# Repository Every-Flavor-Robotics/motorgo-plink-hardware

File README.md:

# MotorGo Plink
## The aim of this project is to make a 4 DC motor drive compatible with the motorgo ecosystem - specifically designed for beginner roboticists.  It should be the form factor of a pihat, but capable of operating entirely on it's own as well. Currently testing release version 1.0!

### Feature list:
- Esp32s3 with Wifi and BT connectivity
- Form factor of a PiHat (we do not currently have the EEPROM requirements of the PiHat Spec)
- DC barrel jack and on-board buck from 6-17V into 5.1V up to 6A  (enough to power pi4 and pi5)
- 9 dof IMU  (LSM6DSOTR-C accel and gyro  +  LIS3MDLTR mag)
- USB-C programming compatible with arduino IDE
- Qwiic port x2 for easy integration with sensors
- Full gpio breakout on 40Pin header + full RPi GPIO passthrough if using as a hat
- 4 bidirectional DC motor channels up to 2A each channel
- 4 Encoder ports for use with EncoderGo 5pin jst for close loop feedback on each motor

### Schematics: 
- Top level

- Motor drivers

- IMU 

- Power system 

- connectors 

### Layout:
- Top - signals components and power

- Inner 1 - GND (I left faint top layer to show ground relative to traces)

- Inner 2 - GND and a tiny tiny power traces where needed

- Bottom - signals and power

- Dimensions

- Full

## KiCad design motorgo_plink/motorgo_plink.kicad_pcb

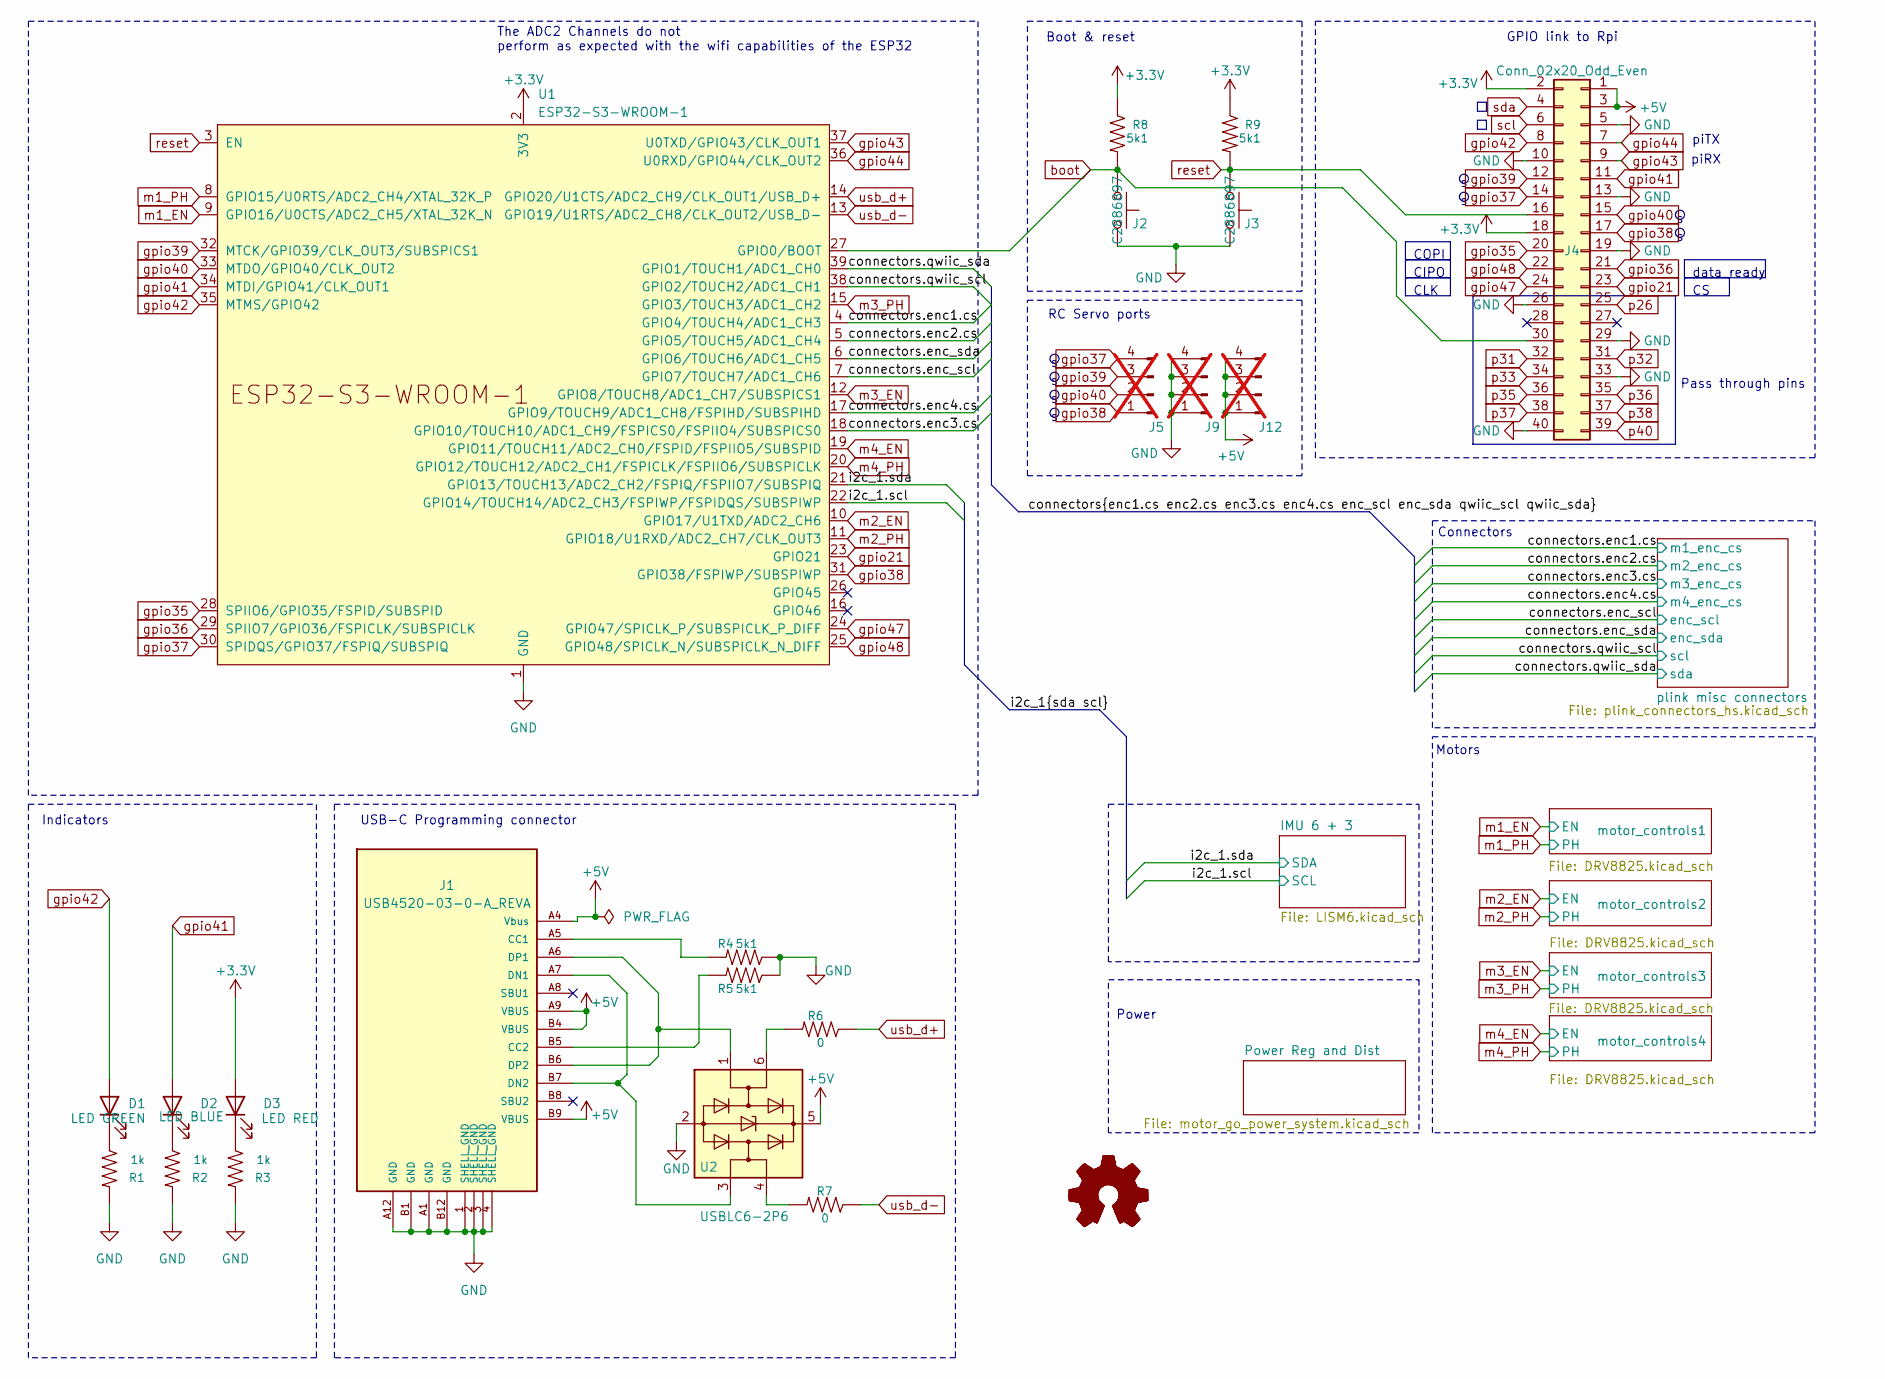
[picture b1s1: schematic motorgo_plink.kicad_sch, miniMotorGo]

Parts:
D1: LED GREEN; LED_0805_2012Metric; LCSC_Part_Number C84259
D2: LED BLUE; LED_0805_2012Metric; LCSC_Part_Number C84260
D3: LED RED; LED_0805_2012Metric; LCSC_Part_Number C84256
J1: USB4520-03-0-A_REVA; USB-C-SMD_TYPEC-303-ACP16; LCSC_Part_Number C720628
J2, J3: C2886897; SW_SPST_TL3342; LCSC_Part_Number C2886897
J4: Conn_02x20_Odd_Even; PinSocket_2x20_P2.54mm_Vertical_SMD; LCSC_Part_Number C3975165
J5, J9, J12: Conn_01x04_Pin; PinHeader_1x04_P2.54mm_Vertical; not fitted
R1, R2, R3: 1k; R_0402_1005Metric; LCSC_Part_Number C11702
R4, R5, R8, R9: 5k1; R_0402_1005Metric; LCSC_Part_Number C25905
R6, R7: 0; R_0402_1005Metric; LCSC_Part_Number C3017451
U1: ESP32-S3-WROOM-1; LCSC_Part_Number C2913198
U2: USBLC6-2P6; SOT-666; LCSC_Part_Number C2827693

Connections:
+3.3V: D3.2 (A), J4.2, J4.18, R8.1, R9.1, U1.2 (3V3); also elsewhere on the board
+5V: J1.A4 (Vbus), J1.A9 (VBUS), J1.B4 (VBUS), J1.B9 (VBUS), J4.1, J4.3, J12.1, J12.2, J12.3, J12.4, U2.5 (VBUS); also elsewhere on the board
/connectors.enc1.cs: U1.4 (GPIO4/TOUCH4/ADC1_CH3); also elsewhere on the board
/connectors.enc2.cs: U1.5 (GPIO5/TOUCH5/ADC1_CH4); also elsewhere on the board
/connectors.enc3.cs: U1.18 (GPIO10/TOUCH10/ADC1_CH9/FSPICS0/FSPIIO4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); also elsewhere on the board
/connectors.enc4.cs: U1.17 (GPIO9/TOUCH9/ADC1_CH8/FSPIHD/SUBSPIHD); also elsewhere on the board
/connectors.enc_scl: U1.7 (GPIO7/TOUCH7/ADC1_CH6); also elsewhere on the board
/connectors.enc_sda: U1.6 (GPIO6/TOUCH6/ADC1_CH5); also elsewhere on the board
/i2c_1.scl: U1.22 (GPIO14/TOUCH14/ADC2_CH3/FSPIWP/FSPIDQS/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); also elsewhere on the board
/i2c_1.sda: U1.21 (GPIO13/TOUCH13/ADC2_CH2/FSPIQ/FSPIIO7/S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); also elsewhere on the board
GND: J1.1 (SHELL_GND), J1.2 (SHELL_GND), J1.3 (SHELL_GND), J1.4 (SHELL_GND), J1.A1 (GND), J1.A12 (GND), J1.B1 (GND), J1.B12 (GND), J2.1, J3.2, J4.5, J4.10, J4.13, J4.19, J4.26, J4.29, J4.33, J4.40, J9.1, J9.2, J9.3, J9.4, R1.2, R2.2, R3.2, R4.1, R5.1, U1.1 (GND), U1.40 (GND), U1.41 (GND), U2.2 (GND); also elsewhere on the board
unnamed: D1.1 (K), R1.1
unnamed: D2.1 (K), R2.1
unnamed: D3.1 (K), R3.1
unnamed: J1.A5 (CC1), R4.2
unnamed: J1.B5 (CC2), R5.2
unnamed: J1.A7 (DN1), J1.B7 (DN2), U2.3 (I/O2)
unnamed: J1.A6 (DP1), J1.B6 (DP2), U2.1 (I/O1)
unnamed: R6.2, U2.6 (I/O1)
unnamed: R7.2, U2.4 (I/O2)
boot: J2.2, J4.30, R8.2, U1.27 (GPIO0/BOOT); also elsewhere on the board
gpio21: J4.23, U1.23 (GPIO21); also elsewhere on the board
gpio35: J4.20, U1.28 (SPIIO6/GPIO35/FSPID/SUBSPID); also elsewhere on the board
gpio36: J4.21, U1.29 (SPIIO7/GPIO36/FSPICLK/SUBSPICLK); also elsewhere on the board
gpio37: J4.14, J5.4, U1.30 (SPIDQS/GPIO37/FSPIQ/SUBSPIQ); also elsewhere on the board
gpio38: J4.17, J5.1, U1.31 (GPIO38/FSPIWP/SUBSPIWP); also elsewhere on the board
gpio39: J4.12, J5.3, U1.32 (MTCK/GPIO39/CLK_OUT3/SUBSPICS1); also elsewhere on the board
gpio40: J4.15, J5.2, U1.33 (MTDO/GPIO40/CLK_OUT2); also elsewhere on the board
gpio41: D2.2 (A), J4.11, U1.34 (MTDI/GPIO41/CLK_OUT1); also elsewhere on the board
gpio42: D1.2 (A), J4.8, U1.35 (MTMS/GPIO42); also elsewhere on the board
gpio43: J4.9, U1.37 (U0TXD/GPIO43/CLK_OUT1); also elsewhere on the board
gpio44: J4.7, U1.36 (U0RXD/GPIO44/CLK_OUT2); also elsewhere on the board
gpio47: J4.24, U1.24 (GPIO47/SPICLK_P/SUBSPICLK_P_DIFF); also elsewhere on the board
gpio48: J4.22, U1.25 (GPIO48/SPICLK_N/SUBSPICLK_N_DIFF); also elsewhere on the board
m1_EN: U1.9 (GPIO16/U0CTS/ADC2_CH5/XTAL_32K_N); also elsewhere on the board
m1_PH: U1.8 (GPIO15/U0RTS/ADC2_CH4/XTAL_32K_P); also elsewhere on the board
m2_EN: U1.10 (GPIO17/U1TXD/ADC2_CH6); also elsewhere on the board
m2_PH: U1.11 (GPIO18/U1RXD/ADC2_CH7/CLK_OUT3); also elsewhere on the board
m3_EN: U1.12 (GPIO8/TOUCH8/ADC1_CH7/SUBSPICS1); also elsewhere on the board
m3_PH: U1.15 (GPIO3/TOUCH3/ADC1_CH2); also elsewhere on the board
m4_EN: U1.19 (GPIO11/TOUCH11/ADC2_CH0/FSPID/FSPIIO5/S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); also elsewhere on the board
m4_PH: U1.20 (GPIO12/TOUCH12/ADC2_CH1/FSPICLK/FSPIIO6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); also elsewhere on the board
p26: J4.25; also elsewhere on the board
p31: J4.32; also elsewhere on the board
p32: J4.31; also elsewhere on the board
p33: J4.34; also elsewhere on the board
p35: J4.36; also elsewhere on the board
p36: J4.35; also elsewhere on the board
p37: J4.38; also elsewhere on the board
p38: J4.37; also elsewhere on the board
p40: J4.39; also elsewhere on the board
reset: J3.1, J4.16, R9.2, U1.3 (EN); also elsewhere on the board
scl: J4.6, U1.38 (GPIO2/TOUCH2/ADC1_CH1); also elsewhere on the board
sda: J4.4, U1.39 (GPIO1/TOUCH1/ADC1_CH0); also elsewhere on the board
usb_d+: R6.1, U1.14 (GPIO20/U1CTS/ADC2_CH9/CLK_OUT1/USB_D+)
usb_d-: R7.1, U1.13 (GPIO19/U1RTS/ADC2_CH8/CLK_OUT2/USB_D-)

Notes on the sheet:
data_ready
CLK
COPI
CIPO
USB-C Programming connector
Motors
Power
Boot & reset
Indicators
piRX
piTX
The ADC2 Channels do not perform as expected with the wifi capabilities of the ESP32
Pass through pins
Connectors
RC Servo ports
GPIO link to Rpi

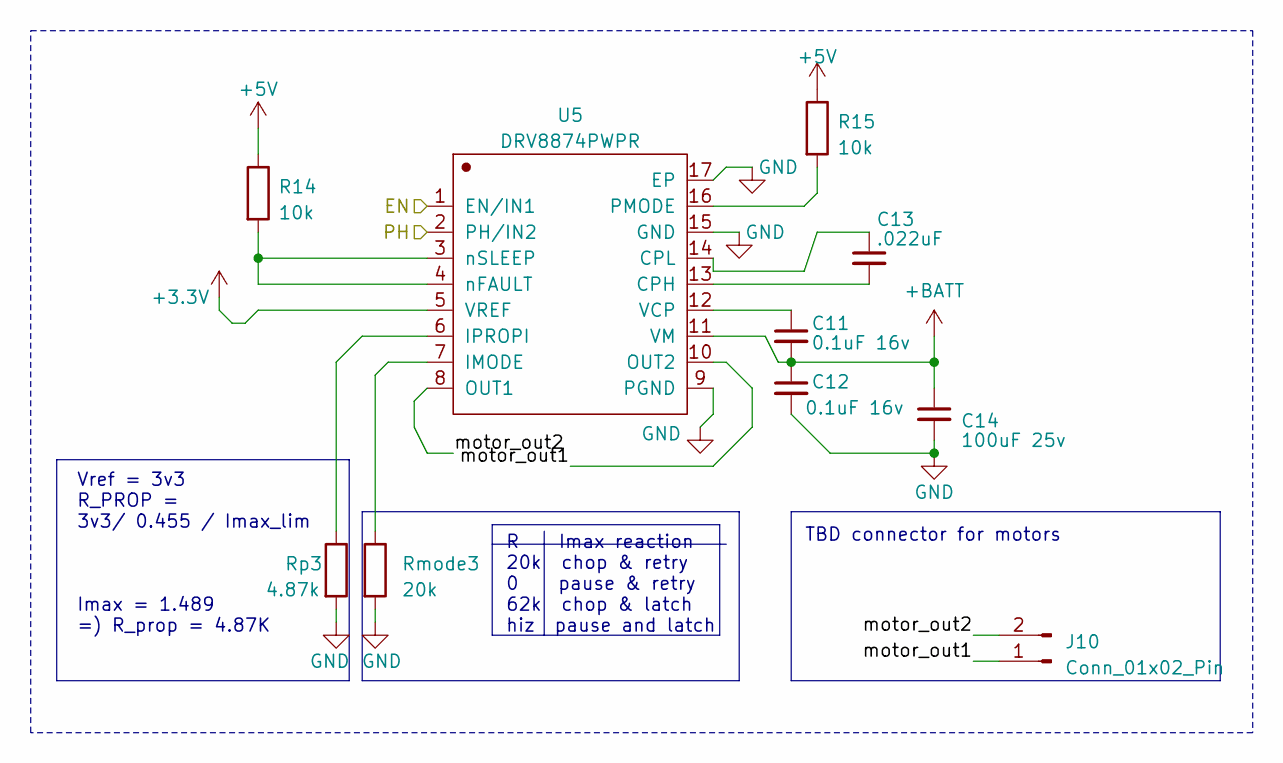
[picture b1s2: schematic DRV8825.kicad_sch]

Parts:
C11, C12: 0.1uF 16v; C_0402_1005Metric; LCSC_Part_Number C3012377
C13: .022uF; C_0402_1005Metric; LCSC_Part_Number C380305
C14: 100uF 25v; C_1210_3225Metric; LCSC_Part_Number C6120014
J10: Conn_01x02_Pin; Molex_KK-254_AE-6410-02A_1x02_P2.54mm_Vertical; LCSC_Part_Number C722716
R14, R15: 10k; R_0402_1005Metric; LCSC_Part_Number C25744
Rmode3: 20k; R_0402_1005Metric; LCSC_Part_Number C3017501
Rp3: 4.87k; R_0402_1005Metric; LCSC_Part_Number C3015971
U5: DRV8874PWPR; HTSSOP-16_L5.0-W4.4-P0.65-LS6.4-BL-EP; LCSC_Part_Number C1855818

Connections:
+3.3V: U5.5 (VREF); also elsewhere on the board
+5V: R14.1, R15.1; also elsewhere on the board
+BATT: C11.2, C12.1, C14.1, U5.11 (VM); also elsewhere on the board
/motor_controls3/motor_out1: J10.1, U5.10 (OUT2)
/motor_controls3/motor_out2: J10.2, U5.8 (OUT1)
GND: C12.2, C14.2, Rmode3.2, Rp3.2, U5.9 (PGND), U5.15 (GND), U5.17 (EP); also elsewhere on the board
unnamed: C13.2, U5.13 (CPH)
unnamed: C13.1, U5.14 (CPL)
unnamed: Rmode3.1, U5.7 (IMODE)
unnamed: Rp3.1, U5.6 (IPROPI)
unnamed: R15.2, U5.16 (PMODE)
unnamed: C11.1, U5.12 (VCP)
unnamed: R14.2, U5.3 (nSLEEP), U5.4 (nFAULT)
m3_EN: U5.1 (EN/IN1); also elsewhere on the board
m3_PH: U5.2 (PH/IN2); also elsewhere on the board

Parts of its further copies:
C3, C4, C7, C8, C26, C27: 0.1uF 16v; C_0402_1005Metric; LCSC_Part_Number C3012377
C5, C9, C28: .022uF; C_0402_1005Metric; LCSC_Part_Number C380305
C6, C10, C29: 100uF 25v; C_1210_3225Metric; LCSC_Part_Number C6120014
J6, J8, J22: Conn_01x02_Pin; Molex_KK-254_AE-6410-02A_1x02_P2.54mm_Vertical; LCSC_Part_Number C722716
R10, R11, R12, R13, R36, R37: 10k; R_0402_1005Metric; LCSC_Part_Number C25744
Rmode1, Rmode2, Rmode4: 20k; R_0402_1005Metric; LCSC_Part_Number C3017501
Rp1, Rp2, Rp4: 4.87k; R_0402_1005Metric; LCSC_Part_Number C3015971
U3, U4, U9: DRV8874PWPR; HTSSOP-16_L5.0-W4.4-P0.65-LS6.4-BL-EP; LCSC_Part_Number C1855818

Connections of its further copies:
+3.3V: U3.5 (VREF), U4.5 (VREF), U9.5 (VREF); also elsewhere on the board
+5V: R10.1, R11.1, R12.1, R13.1, R36.1, R37.1; also elsewhere on the board
+BATT: C3.2, C4.1, C6.1, C7.2, C8.1, C10.1, C26.2, C27.1, C29.1, U3.11 (VM), U4.11 (VM), U9.11 (VM); also elsewhere on the board
/motor_controls1/motor_out1: J8.1, U4.10 (OUT2)
/motor_controls1/motor_out2: J8.2, U4.8 (OUT1)
/motor_controls2/motor_out1: J6.1, U3.10 (OUT2)
/motor_controls2/motor_out2: J6.2, U3.8 (OUT1)
/motor_controls4/motor_out1: J22.1, U9.10 (OUT2)
/motor_controls4/motor_out2: J22.2, U9.8 (OUT1)
GND: C4.2, C6.2, C8.2, C10.2, C27.2, C29.2, Rmode1.2, Rmode2.2, Rmode4.2, Rp1.2, Rp2.2, Rp4.2, U3.9 (PGND), U3.15 (GND), U3.17 (EP), U4.9 (PGND), U4.15 (GND), U4.17 (EP), U9.9 (PGND), U9.15 (GND), U9.17 (EP); also elsewhere on the board
unnamed: C5.2, U3.13 (CPH)
unnamed: C5.1, U3.14 (CPL)
unnamed: Rmode1.1, U3.7 (IMODE)
unnamed: Rp1.1, U3.6 (IPROPI)
unnamed: R11.2, U3.16 (PMODE)
unnamed: C3.1, U3.12 (VCP)
unnamed: R10.2, U3.3 (nSLEEP), U3.4 (nFAULT)
unnamed: C9.2, U4.13 (CPH)
unnamed: C9.1, U4.14 (CPL)
unnamed: Rmode2.1, U4.7 (IMODE)
unnamed: Rp2.1, U4.6 (IPROPI)
unnamed: R13.2, U4.16 (PMODE)
unnamed: C7.1, U4.12 (VCP)
unnamed: R12.2, U4.3 (nSLEEP), U4.4 (nFAULT)
unnamed: C28.2, U9.13 (CPH)
unnamed: C28.1, U9.14 (CPL)
unnamed: Rmode4.1, U9.7 (IMODE)
unnamed: Rp4.1, U9.6 (IPROPI)
unnamed: R37.2, U9.16 (PMODE)
unnamed: C26.1, U9.12 (VCP)
unnamed: R36.2, U9.3 (nSLEEP), U9.4 (nFAULT)
m1_EN: U4.1 (EN/IN1); also elsewhere on the board
m1_PH: U4.2 (PH/IN2); also elsewhere on the board
m2_EN: U3.1 (EN/IN1); also elsewhere on the board
m2_PH: U3.2 (PH/IN2); also elsewhere on the board
m4_EN: U9.1 (EN/IN1); also elsewhere on the board
m4_PH: U9.2 (PH/IN2); also elsewhere on the board

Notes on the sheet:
Vref = 3v3 R_PROP = 3v3/ 0.455 / Imax_lim
TBD connector for motors
Imax = 1.489 =) R_prop = 4.87K
R Imax reaction 20k chop & retry 0 pause & retry 62k chop & latch hiz pause and latch

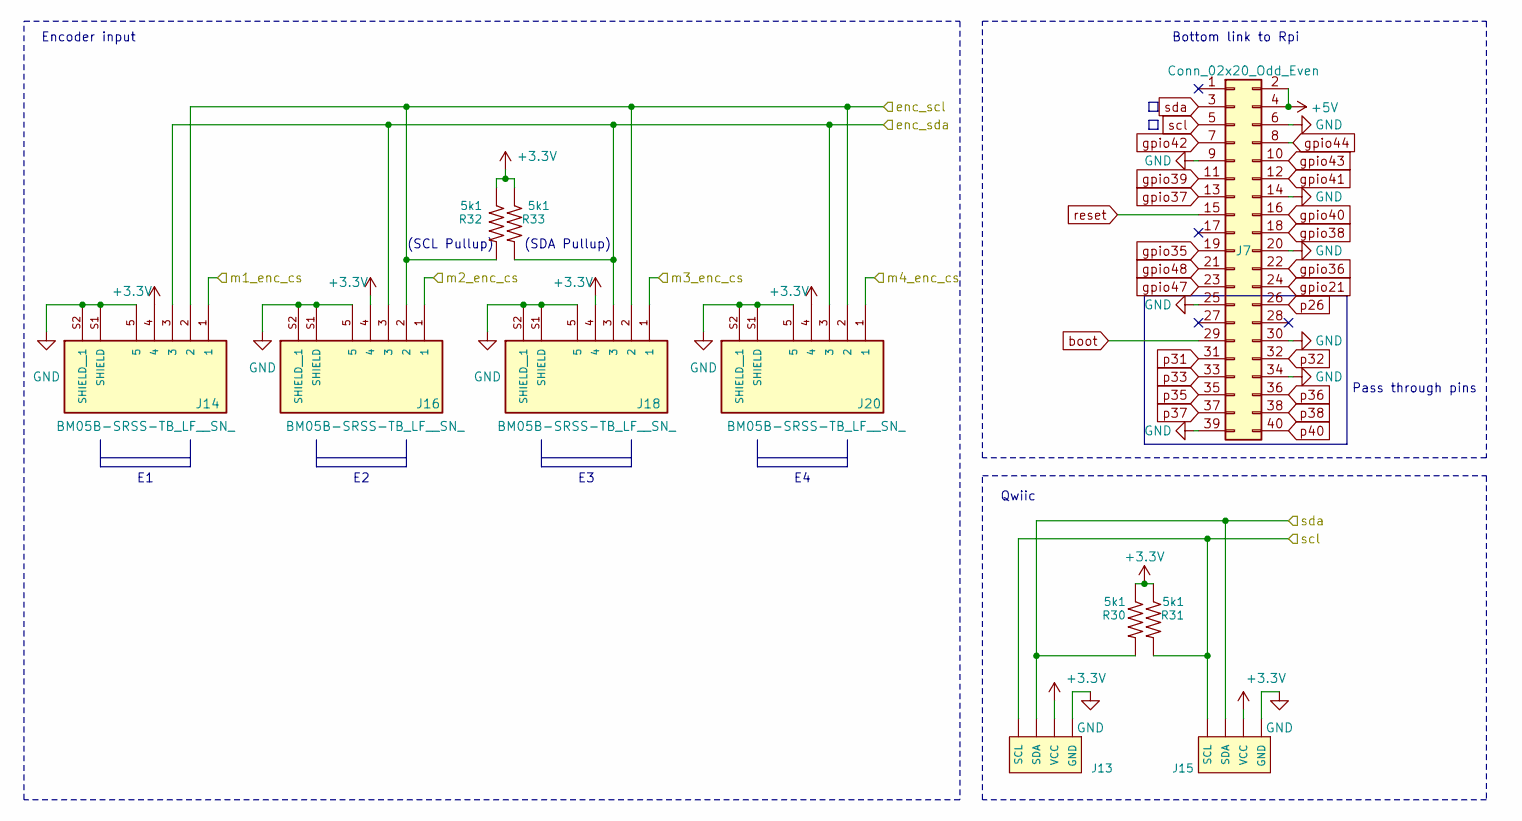
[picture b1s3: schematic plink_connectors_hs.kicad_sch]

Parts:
J7: Conn_02x20_Odd_Even; PinSocket_2x20_P2.54mm_Vertical_SMD; LCSC_Part_Number C3975165
J13, J15: I2C_STANDARDQWIIC; JST_SH_BM04B-SRSS-TB_1x04-1MP_P1.00mm_Vertical; LCSC_Part_Number C160404
J14, J16, J18, J20: BM05B-SRSS-TB_LF__SN_; JST_BM05B-SRSS-TB_LF__SN_; PARTREV N/A; LCSC_Part_Number C265092
R30, R31, R32, R33: 5k1; R_0402_1005Metric; LCSC_Part_Number C25905

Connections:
+3.3V: J13.2 (VCC), J14.4, J15.2 (VCC), J16.4, J18.4, J20.4, R30.1, R31.1, R32.1, R33.1; also elsewhere on the board
+5V: J7.2, J7.4; also elsewhere on the board
/connectors.enc1.cs: J14.1; also elsewhere on the board
/connectors.enc2.cs: J16.1; also elsewhere on the board
/connectors.enc3.cs: J18.1; also elsewhere on the board
/connectors.enc4.cs: J20.1; also elsewhere on the board
/connectors.enc_scl: J14.2, J16.2, J18.2, J20.2, R32.2; also elsewhere on the board
/connectors.enc_sda: J14.3, J16.3, J18.3, J20.3, R33.2; also elsewhere on the board
GND: J7.6, J7.9, J7.14, J7.20, J7.25, J7.30, J7.34, J7.39, J13.1 (GND), J14.5, J14.S1 (SHIELD), J14.S2 (SHIELD__1), J15.1 (GND), J16.5, J16.S1 (SHIELD), J16.S2 (SHIELD__1), J18.5, J18.S1 (SHIELD), J18.S2 (SHIELD__1), J20.5, J20.S1 (SHIELD), J20.S2 (SHIELD__1); also elsewhere on the board
boot: J7.29; also elsewhere on the board
gpio21: J7.24; also elsewhere on the board
gpio35: J7.19; also elsewhere on the board
gpio36: J7.22; also elsewhere on the board
gpio37: J7.13; also elsewhere on the board
gpio38: J7.18; also elsewhere on the board
gpio39: J7.11; also elsewhere on the board
gpio40: J7.16; also elsewhere on the board
gpio41: J7.12; also elsewhere on the board
gpio42: J7.7; also elsewhere on the board
gpio43: J7.10; also elsewhere on the board
gpio44: J7.8; also elsewhere on the board
gpio47: J7.23; also elsewhere on the board
gpio48: J7.21; also elsewhere on the board
p26: J7.26; also elsewhere on the board
p31: J7.31; also elsewhere on the board
p32: J7.32; also elsewhere on the board
p33: J7.33; also elsewhere on the board
p35: J7.35; also elsewhere on the board
p36: J7.36; also elsewhere on the board
p37: J7.37; also elsewhere on the board
p38: J7.38; also elsewhere on the board
p40: J7.40; also elsewhere on the board
reset: J7.15; also elsewhere on the board
scl: J7.5, J13.4 (SCL), J15.4 (SCL), R31.2; also elsewhere on the board
sda: J7.3, J13.3 (SDA), J15.3 (SDA), R30.2; also elsewhere on the board

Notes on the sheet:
Qwiic
Bottom link to Rpi
Encoder input
(SCL Pullup)
Pass through pins
(SDA Pullup)

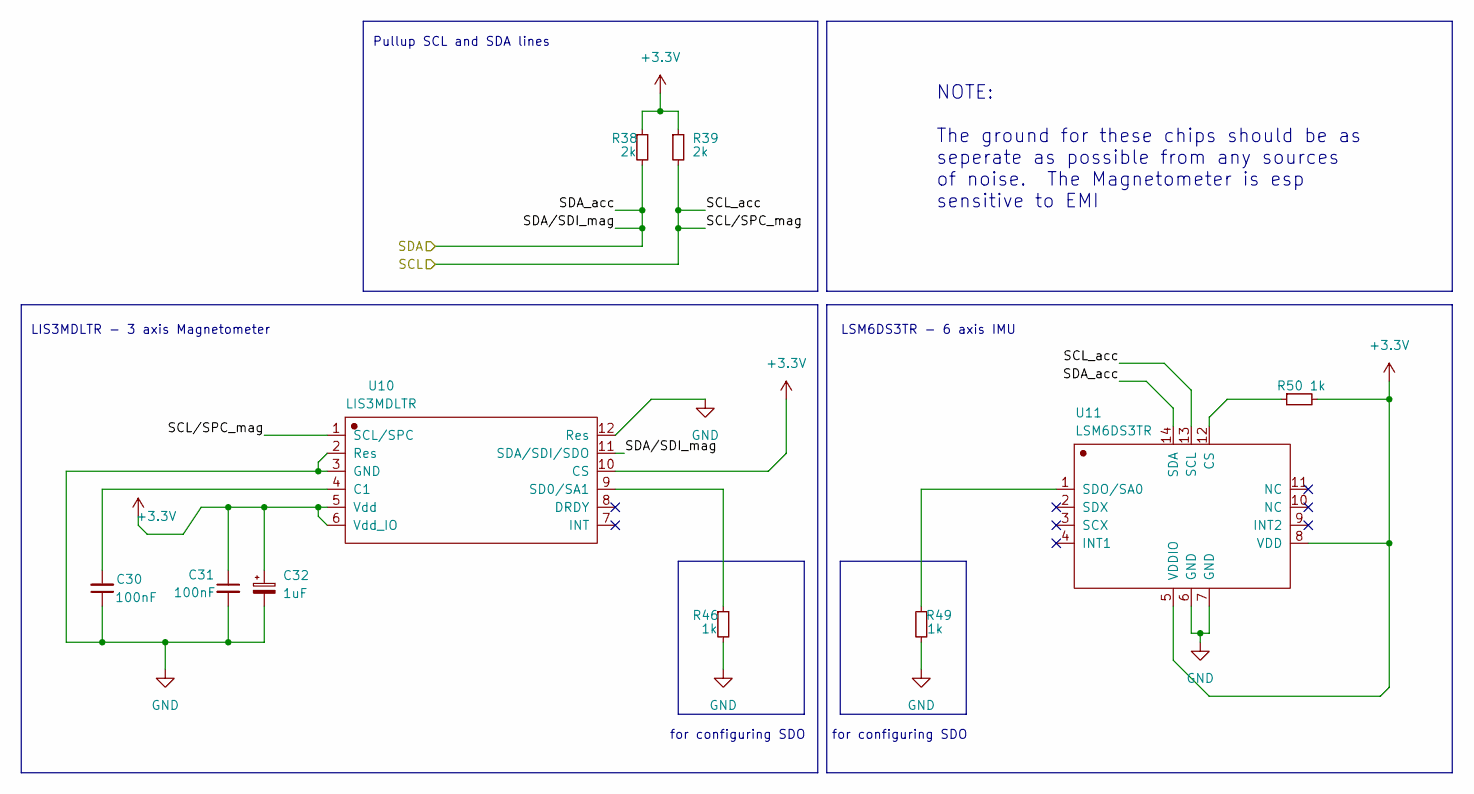
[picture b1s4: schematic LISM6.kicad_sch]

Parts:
C30, C31: 100nF; C_0402_1005Metric; LCSC_Part_Number C880603
C32: 1uF; C_0603_1608Metric; LCSC_Part_Number C15849
R38, R39: 2k; R_0402_1005Metric; LCSC_Part_Number C4109
R46, R49, R50: 1k; R_0402_1005Metric; LCSC_Part_Number C11702
U10: LIS3MDLTR; LIS3MDLTR_LGA-12; LCSC_Part_Number C478483
U11: LSM6DS3TR; LSM6DSOTR_LGA-14; LCSC_Part_Number C95230

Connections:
+3.3V: C31.1, C32.1, R38.1, R39.1, R50.2, U10.5 (Vdd), U10.6 (Vdd_IO), U10.10 (CS), U11.5 (VDDIO), U11.8 (VDD); also elsewhere on the board
/i2c_1.scl: R39.2, U10.1 (SCL/SPC), U11.13 (SCL); also elsewhere on the board
/i2c_1.sda: R38.2, U10.11 (SDA/SDI/SDO), U11.14 (SDA); also elsewhere on the board
GND: C30.1, C31.2, C32.2, R46.2, R49.2, U10.2 (Res), U10.3 (GND), U10.12 (Res), U11.6 (GND), U11.7 (GND); also elsewhere on the board
unnamed: C30.2, U10.4 (C1)
unnamed: R46.1, U10.9 (SD0/SA1)
unnamed: R50.1, U11.12 (CS)
unnamed: R49.1, U11.1 (SDO/SA0)

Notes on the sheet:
NOTE: The ground for these chips should be as seperate as possible from any sources of noise. The Magnetometer is esp sensitive to EMI
for configuring SDO
LSM6DS3TR - 6 axis IMU
Pullup SCL and SDA lines
LIS3MDLTR - 3 axis Magnetometer

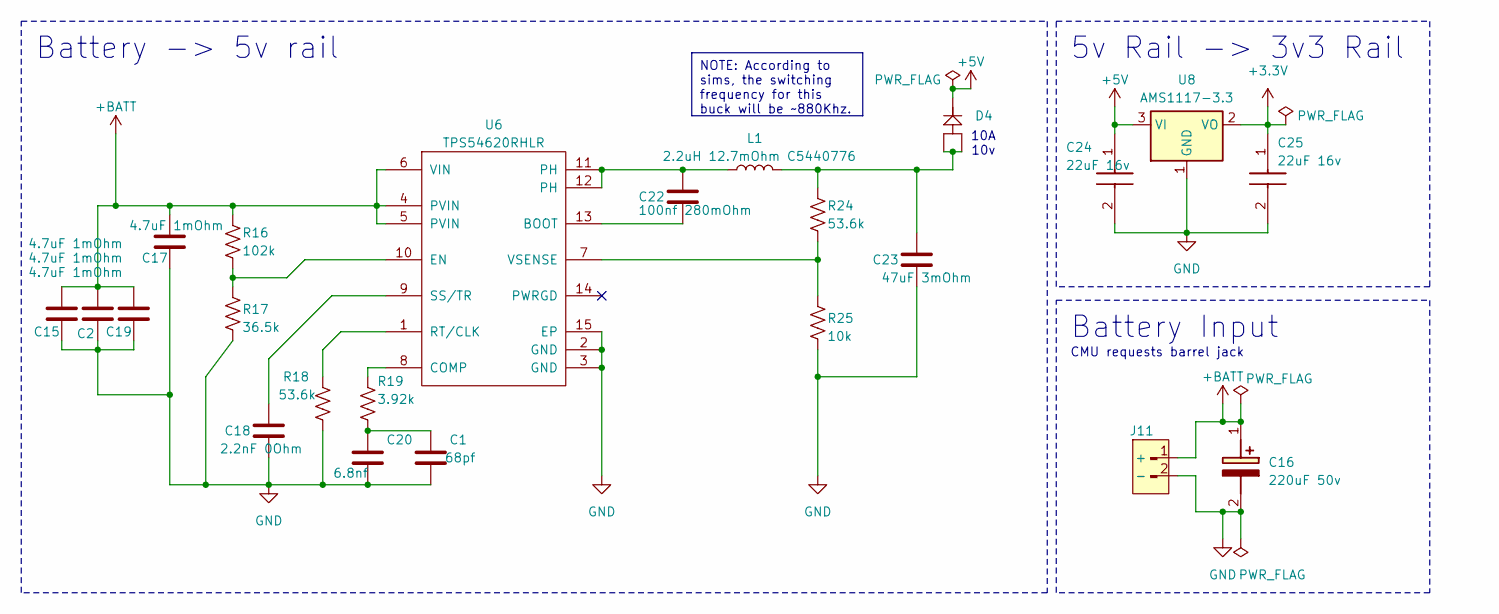
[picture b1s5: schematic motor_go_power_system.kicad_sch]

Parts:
C1: 68pf; C_0402_1005Metric; LCSC_Part_Number C3037638
C2, C15, C19: 4.7uF 1mOhm; C_0805_2012Metric; LCSC_Part_Number C5448891
C16: 220uF 50v; CP_Elec_10x10; Mouser Part Number 140-RGA221M1EBK0811G
C17: 4.7uF 1mOhm; C_0603_1608Metric; LCSC_Part_Number C6119856
C18: 2.2nF 0Ohm; C_0402_1005Metric; LCSC_Part_Number C285033
C20: 6.8nf; C_0402_1005Metric; LCSC_Part_Number C3037638
C22: 100nf 280mOhm; C_0402_1005Metric; LCSC_Part_Number C880603
C23: 47uF 3mOhm; C_1210_3225Metric; LCSC_Part_Number C7432791
C24, C25: 22uF 16v; C_0603_1608Metric; Mouser Part Number 187-CL21A226MQQNNNE
D4: Schottky_SB1045L_C908747 10A; TO-277_3P-L5.4-W4.0-LS6.5-TR; LCSC_Part_Number C908747
J11: CONN-TH_DC-005-2.5A-2.0; LCSC_Part_Number C319099
L1: 2.2uH 12.7mOhm C5440776; IND-SMD_L6.6-W6.4_CKSTT0610; LCSC_Part_Number C5440776
R16: 102k; R_0402_1005Metric; LCSC_Part_Number C2933066
R17: 36.5k; R_0402_1005Metric; LCSC_Part_Number C25887
R18: 53.6k; R_0402_1005Metric; LCSC_Part_Number C5153961
R19: 3.92k; R_0402_1005Metric; LCSC_Part_Number C3013164
R24: 53.6k; R_0402_1005Metric; LCSC_Part_Number C2998086
R25: 10k; R_0402_1005Metric; LCSC_Part_Number C2906885
U6: TPS54620RHLR; VQFN-14_L3.5-W3.5-P0.50-TL-EP_TPS54622RHLT; LCSC_Part_Number C263274
U8: AMS1117-3.3; SOT-223-3_TabPin2; LCSC_Part_Number C347222

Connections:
+3.3V: C25.1, U8.2 (VO); also elsewhere on the board
+5V: C24.1, D4.2 (K), U8.3 (VI); also elsewhere on the board
+BATT: C2.1, C15.1, C16.1 (+), C17.1, C19.1, J11.1 (+), R16.1, U6.4 (PVIN), U6.5 (PVIN), U6.6 (VIN); also elsewhere on the board
GND: C1.2, C2.2, C15.2, C16.2 (-), C17.2, C18.2, C19.2, C20.2, C23.2, C24.2, C25.2, J11.2 (-), R17.2, R18.2, R25.2, U6.2 (GND), U6.3 (GND), U6.15 (EP), U8.1 (GND); also elsewhere on the board
unnamed: C1.1, C20.1, R19.2
unnamed: C22.1, L1.1, U6.11 (PH), U6.12 (PH)
unnamed: C23.1, D4.1 (A), D4.3 (A), L1.2, R24.1
unnamed: C22.2, U6.13 (BOOT)
unnamed: R19.1, U6.8 (COMP)
unnamed: R16.2, R17.1, U6.10 (EN)
unnamed: R18.1, U6.1 (RT/CLK)
unnamed: C18.1, U6.9 (SS/TR)
unnamed: R24.2, R25.1, U6.7 (VSENSE)

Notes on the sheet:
NOTE: According to sims, the switching frequency for this buck will be ~880Khz.
10A 10v
Battery -> 5v rail
CMU requests barrel jack
Battery Input
5v Rail -> 3v3 Rail

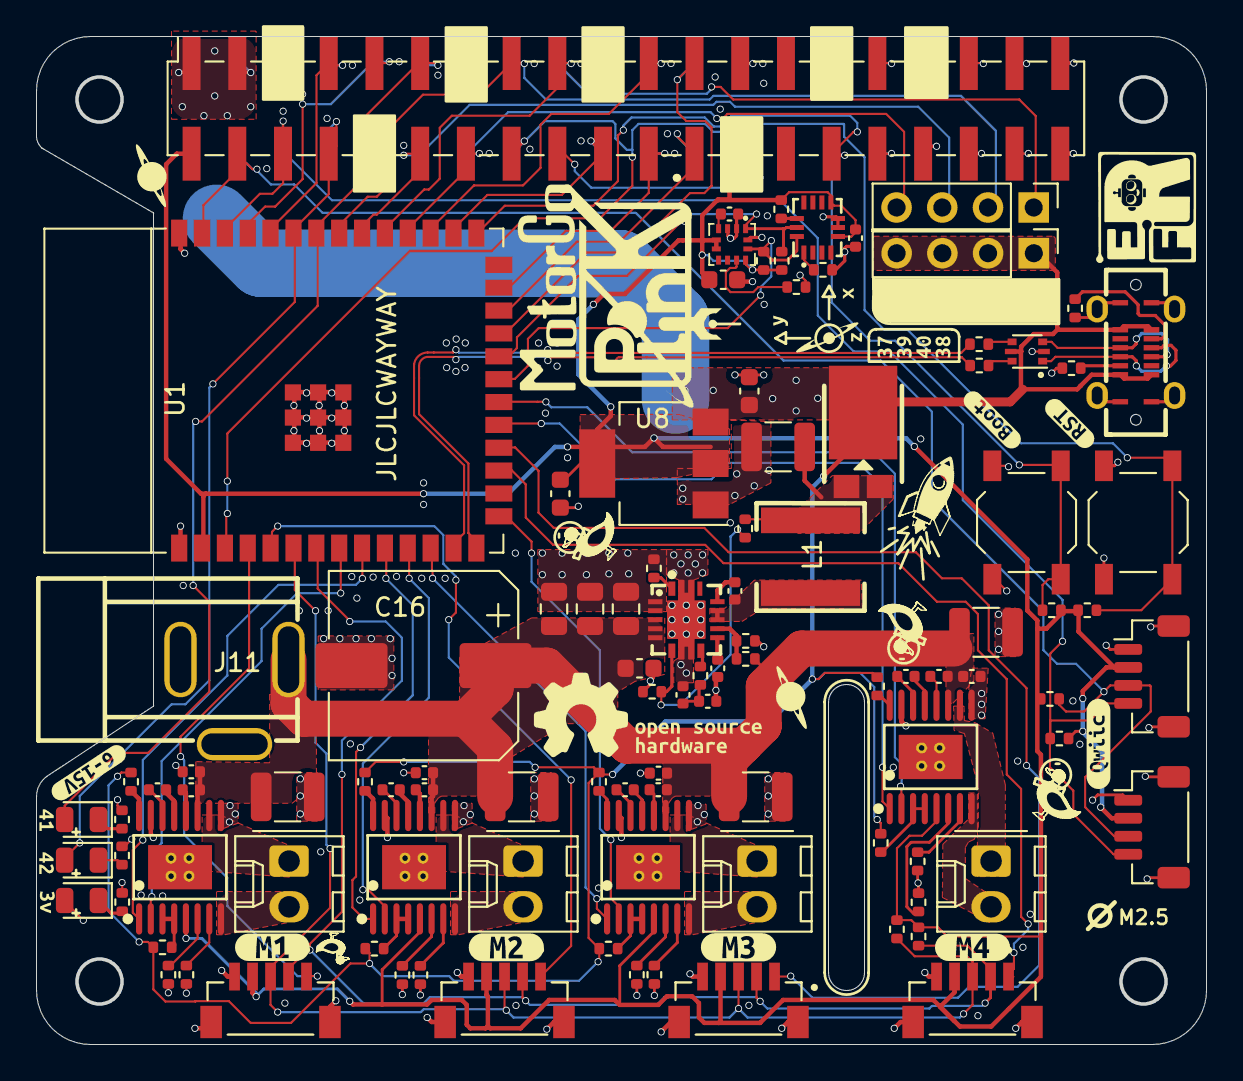
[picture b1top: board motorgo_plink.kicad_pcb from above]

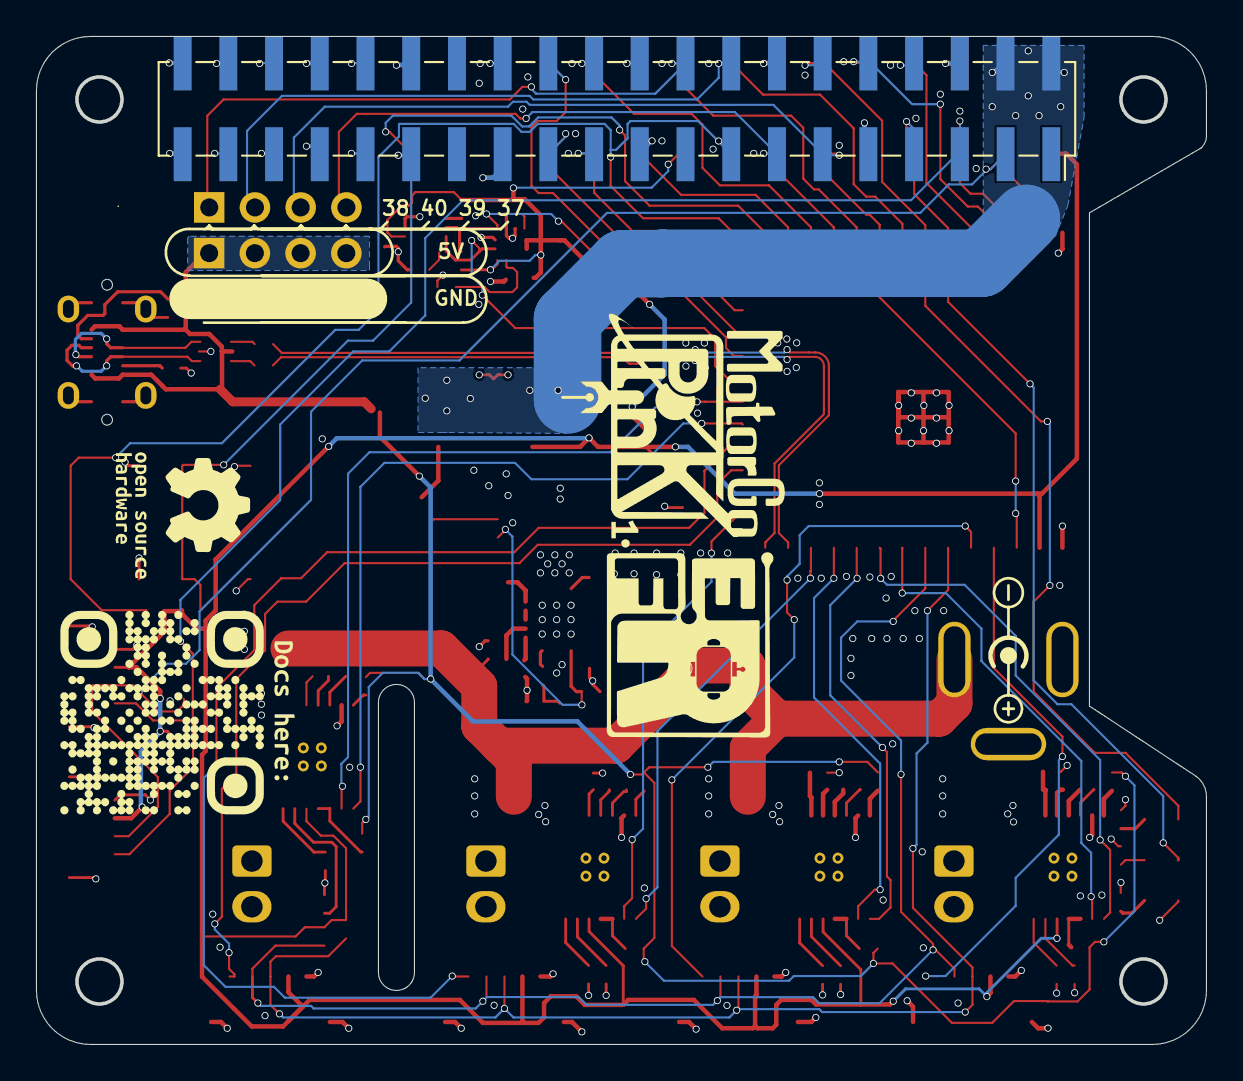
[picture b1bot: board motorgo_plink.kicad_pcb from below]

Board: 4 copper layers, 65.0 x 56.0 mm, 124 parts (4 on the bottom side), 106 nets.

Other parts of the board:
kibuzzard-670F41F1: G***; kibuzzard-670F41F1
kibuzzard-673F56EA: G***; kibuzzard-673F56EA
kibuzzard-673F56F0: G***; kibuzzard-673F56F0
kibuzzard-673F81B9, kibuzzard-673F81B9#2: G***; kibuzzard-673F81B9
kibuzzard-673F82C5: G***; kibuzzard-673F82C5
kibuzzard-673F82D0: G***; kibuzzard-673F82D0
kibuzzard-673F82DC: G***; kibuzzard-673F82DC
kibuzzard-673F85FE: G***; kibuzzard-673F85FE
kibuzzard-673F953E: G***; kibuzzard-673F953E
kibuzzard-67320F9F: G***; kibuzzard-67320F9F
kibuzzard-67320F82: G***; kibuzzard-67320F82
kibuzzard-67324B68: G***; kibuzzard-67324B68
kibuzzard-67324C8A: G***; kibuzzard-67324C8A
kibuzzard-67324C73: G***; kibuzzard-67324C73
kibuzzard-67324C97: G***; kibuzzard-67324C97
kibuzzard-67324CB2: G***; kibuzzard-67324CB2
kibuzzard-67401FB8: G***; kibuzzard-67401FB8
kibuzzard-673237E1: G***; kibuzzard-673237E1

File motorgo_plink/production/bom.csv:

Designator,Footprint,Quantity,Value,LCSC Part #
C1,0402,1,68pf,
"C10, C14, C29, C6",1210,4,100uF 25v,
"C11, C12, C26, C27, C3, C4, C7, C8",0402,8,0.1uF 16v,
"C13, C28, C5, C9",0402,4,.022uF,
"C15, C19, C2",0805,3,4.7uF 1mOhm,
C16,CP_Elec_10x10,1,220uF 50v,
C17,0603,1,4.7uF 1mOhm,
C18,0402,1,2.2nF 0Ohm,
C20,0402,1,6.8nf,
C22,0402,1,100nf 280mOhm,
C23,1210,1,47uF 3mOhm,
"C24, C25",0603,2,22uF 16v,
"C30, C31",0402,2,100nF,
C32,0603,1,1uF,
D1,0805,1,LED GREEN,
D2,0805,1,LED BLUE,
D3,0805,1,LED RED,
D4,TO-277_3P-L5.4-W4.0-LS6.5-TR,1,Schottky_SB1045L_C908747 10A,
J1,USB-C-SMD_TYPEC-303-ACP16,1,USB4520-03-0-A_REVA,
"J10, J22, J6, J8",Molex_KK-254_AE-6410-02A_1x02_P2.54mm_Vertical,4,Conn_01x02_Pin,
J11,CONN-TH_DC-005-2.5A-2.0,1,~,
"J13, J15",JST_SH_BM04B-SRSS-TB_1x04-1MP_P1.00mm_Vertical,2,I2C_STANDARDQWIIC,
"J14, J16, J18, J20",JST_BM05B-SRSS-TB_LF__SN_,4,BM05B-SRSS-TB_LF__SN_,
"J2, J3",SW_SPST_TL3342,2,C2886897,
"J4, J7",PinSocket_2x20_P2.54mm_Vertical_SMD,2,Conn_02x20_Odd_Even,
L1,IND-SMD_L6.6-W6.4_CKSTT0610,1,2.2uH 12.7mOhm C5440776,
"R1, R2, R3, R46, R49, R50",0402,6,1k,
"R10, R11, R12, R13, R14, R15, R25, R36, R37",0402,9,10k,
R16,0402,1,102k,
R17,0402,1,36.5k,
"R18, R24",0402,2,53.6k,
R19,0402,1,3.92k,
"R30, R31, R32, R33, R4, R5, R8, R9",0402,8,5k1,
"R38, R39",0402,2,2k,
"R6, R7",0402,2,0,
"RMODE1, RMODE2, RMODE3, RMODE4",0402,4,20k,
"RP1, RP2, RP3, RP4",0402,4,4.87k,
U1,ESP32-S3-WROOM-1,1,ESP32-S3-WROOM-1,
U10,LIS3MDLTR_LGA-12,1,LIS3MDLTR,
U11,LSM6DSOTR_LGA-14,1,LSM6DS3TR,
U2,SOT-666,1,USBLC6-2P6,
"U3, U4, U5, U9",HTSSOP-16_L5.0-W4.4-P0.65-LS6.4-BL-EP,4,DRV8874PWPR,
U6,VQFN-14_L3.5-W3.5-P0.50-TL-EP_TPS54622RHLT,1,TPS54620RHLR,
U8,SOT-223-3_TabPin2,1,AMS1117-3.3,

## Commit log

2024-05-22 first commit with base project
2024-05-22 added board blank file
2024-05-22 added project specific libraries
2024-05-28 WIP update for BOM co-work
2024-05-29 WIP update, schematic mainly complete
2024-05-30 WIP update. Parts semi-finalized
2024-05-30 WIP update. Layout begin
2024-05-31 WIP update. Ready for BOM editing
2024-05-31 WIP - adding P/Ns to BOM (TS). will finish in afternoon.
2024-05-31 finished first pass on BOM. check 100uF cap and a couple others. TS
2024-05-31 swap electrolytic with MLCC cap. TS
2024-05-31 replaced female 2x20 header with brick nogging. male pin headers listed in the google sheets.
2024-06-02 WIP update. change USBC port
2024-06-03 ready for order
2024-06-03 fix DRC errors
2024-06-03 WIP (TS) - updating BOM with values from other branch.
2024-06-03 fix C31 and C30
2024-06-03 updated BOM in prep for order - TS
2024-06-04 added J11 p/n - TS
2024-10-09 wip culling of non-vital schematic components
2024-10-10 wip culling schematics and removing tracks
2024-10-14 wip schematic edits to account for buck reg design
2024-10-15 wip layout work begun, board dimensions finalized
2024-10-16 layout complete! checkpoint ready for design review
2024-10-16 silkscreen added and DRC satisfied
2024-10-17 production files and all edits for final send off of v1.0
2024-10-17 added schematic pdf and removed vestigal files
2024-10-17 removed old design docs
2024-11-11 added schottky diode to local libraries
2024-11-11 added symbols and footprints to local libraries
2024-11-11 updated schematic to fix IMU i2c mismatch, silkscreen readability, schottky backpower diode, and added RC Servo pins
2024-11-11 added sym and lib tables to github repo
2024-11-11 added fp-lib-table to repo
2024-11-11 updated git ignore to include cache files generated by kicad
2024-11-11 removed info-cache file from repo
2024-11-11 edit gitignore
2024-11-11 added soldermask on back of board for mounting holes
2025-01-08 update to recent production files
